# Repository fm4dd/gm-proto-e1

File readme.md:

## GM-PROTO-E1

### Description

The gm-proto-e1 board is an application module board for the <a href="https://www.colognechip.com/programmable-logic/gatemate-evaluation-board/">GateMate FPGA evaluation board E1</a>, made by <a href="https://www.colognechip.com/">Cologne Chip</a>. It connects to the evaluation board through the GPIO bank headers, and its main feature is the 20x19 standard 2.54mm pitch prototyping area. 36 FPGA signals from GPIO banks SB, EA and EB are brought in to enable easy experimentation for connecting FPGA board peripherals. In addition, the application board provides a minimal set of data input/output components for basic FPGA interactions. Two variants have been designed: One for through-hole components, one for higher density SMD parts:

- 2x push buttons THT / 3x push buttons SMD
- 4x slide switches THT / 8x DIP switches SMD
- 4x LED THT / 8x LED SMD
- 2x 7-Segment display modules
- Buzzer (SMD only)

This design is registered under the OSHWA Open Source Hardware Self-Certification:  

### Hardware Versions

The gm-proto-e1 application board has been designed as a 100x70mm double-layer PCB, with precision alignment of the six 46-pin 1.27mm pitch GPIO connectors, verified to fit the GateMate FPGA evaluation board E1 V3.1B. For THT components, great care needs to be taken to cut pins flush during soldering and prevent them from reaching components of the evaluation board below. The 1.27mm pitch GPIO connectors are offered with different distance spacers (2, 2.5 and 5mm), and the standard spacers achieve only 5mm total clearance.

#### Through-hole Design:

| Version | Gerber | Schema |
|---------|--------|--------|
| 1.0     |[20220914-gm-proto-e1-gerber.zip](fabfiles-tht/v10/20220914-gm-proto-e1-gerber.zip) | [20220914-gm-proto-e1-schematic.pdf](fabfiles-tht/v10/20220914-gm-proto-e1-schematic.pdf) |

#### Surface-Mount Design:

| Version | Gerber | Schema |
|---------|--------|--------|
| 1.0     |[20220923-gm-proto-e1-gerber.zip](fabfiles-smd/v10/20220923-gm-proto-e1-gerber.zip) | [20220923-gm-proto-e1-schematic.pdf](fabfiles-smd/v10/20220923-gm-proto-e1-schematic.pdf) |

### Pin Assignments

Due to IO differences between THT and SMD board variants, they have different pinouts:

#### Through-hole Design:

- IO pinout assigments file: [pin-assignment-tht.md](pin-assignment-tht.md)
- hardware constraints file: [gm-proto-e1-tht.ccf](examples-tht/gm-proto-e1-tht.ccf)

#### Surface-Mount Design:

- IO pinout assigments file: [pin-assignment-smd.md](pin-assignment-smd.md)
- hardware constraints file: [gm-proto-e1-smd.ccf](examples-smd/gm-proto-e10-smd.ccf)

Note: Components are prefixed with "pr", to identify them belonging to the gm-proto-e1 application board. For prototyping, 36 IO signals from GPIO banks SB, EA and EB have been placed into the 2.54mm area border pin rows.

### Example Code

The following code examples demonstrate the board input/output components for quick verification. The code has been tested with the pre-compiled opensource toolchain released through the GateMate support site at <a href="https://www.colognechip.com/mygatemate/">https://www.colognechip.com/mygatemate/</a>

#### Through-hole Design:

| Language | Folder                       | Description                                                       |
|----------|------------------------------|-------------------------------------------------------------------|
| Verilog  |[blink](examples-tht/blink)   | blinks two LED's in a alternating pattern                         |
| Verilog  |[count](examples-tht/count)   | binary counter displayed on four LED and two 7-Segment digits     |
| Verilog  |[button](examples-tht/button) | push button press changes LED frequency and light move direction  |
| Verilog  |[switch](examples-tht/switch) | each slide switch turns its corresponding LED on or off           |
| Verilog  |[display](examples-tht/display)| basic control of a HD44780-compatible 3.3V character LCD display  |
| Verilog  |[rotenc16](examples-tht/rotenc16)| basic control of a 16-position rotary encoder input switch  |

#### Surface-Mount Design:

| Language | Folder                        | Description                                                       |
|----------|-------------------------------|-------------------------------------------------------------------|
| Verilog  |[blink](examples-smd/blink)    | blinks four LED's in a alternating pattern                        |
| Verilog  |[count](examples-smd/count)    | binary counter displayed on eight LED and two 7-Segment digits    |
| Verilog  |[button](examples-smd/button)  | push button press changes LED frequency and light move direction  |
| Verilog  |[switch](examples-smd/switch)  | each slide switch turns its corresponding LED on or off           |

### Board Pictures

The gm-proto-e1 THT board, before and after assembly.

The gm-proto-e1 THT board has been designed with KiCad version 6.0.

The gm-proto-e1 THT board mounted on the E1 board, running the "count" demo.

The gm-proto-e1 THT board hardware verification video.

The gm-proto-e1 THT board, running the "display" demo

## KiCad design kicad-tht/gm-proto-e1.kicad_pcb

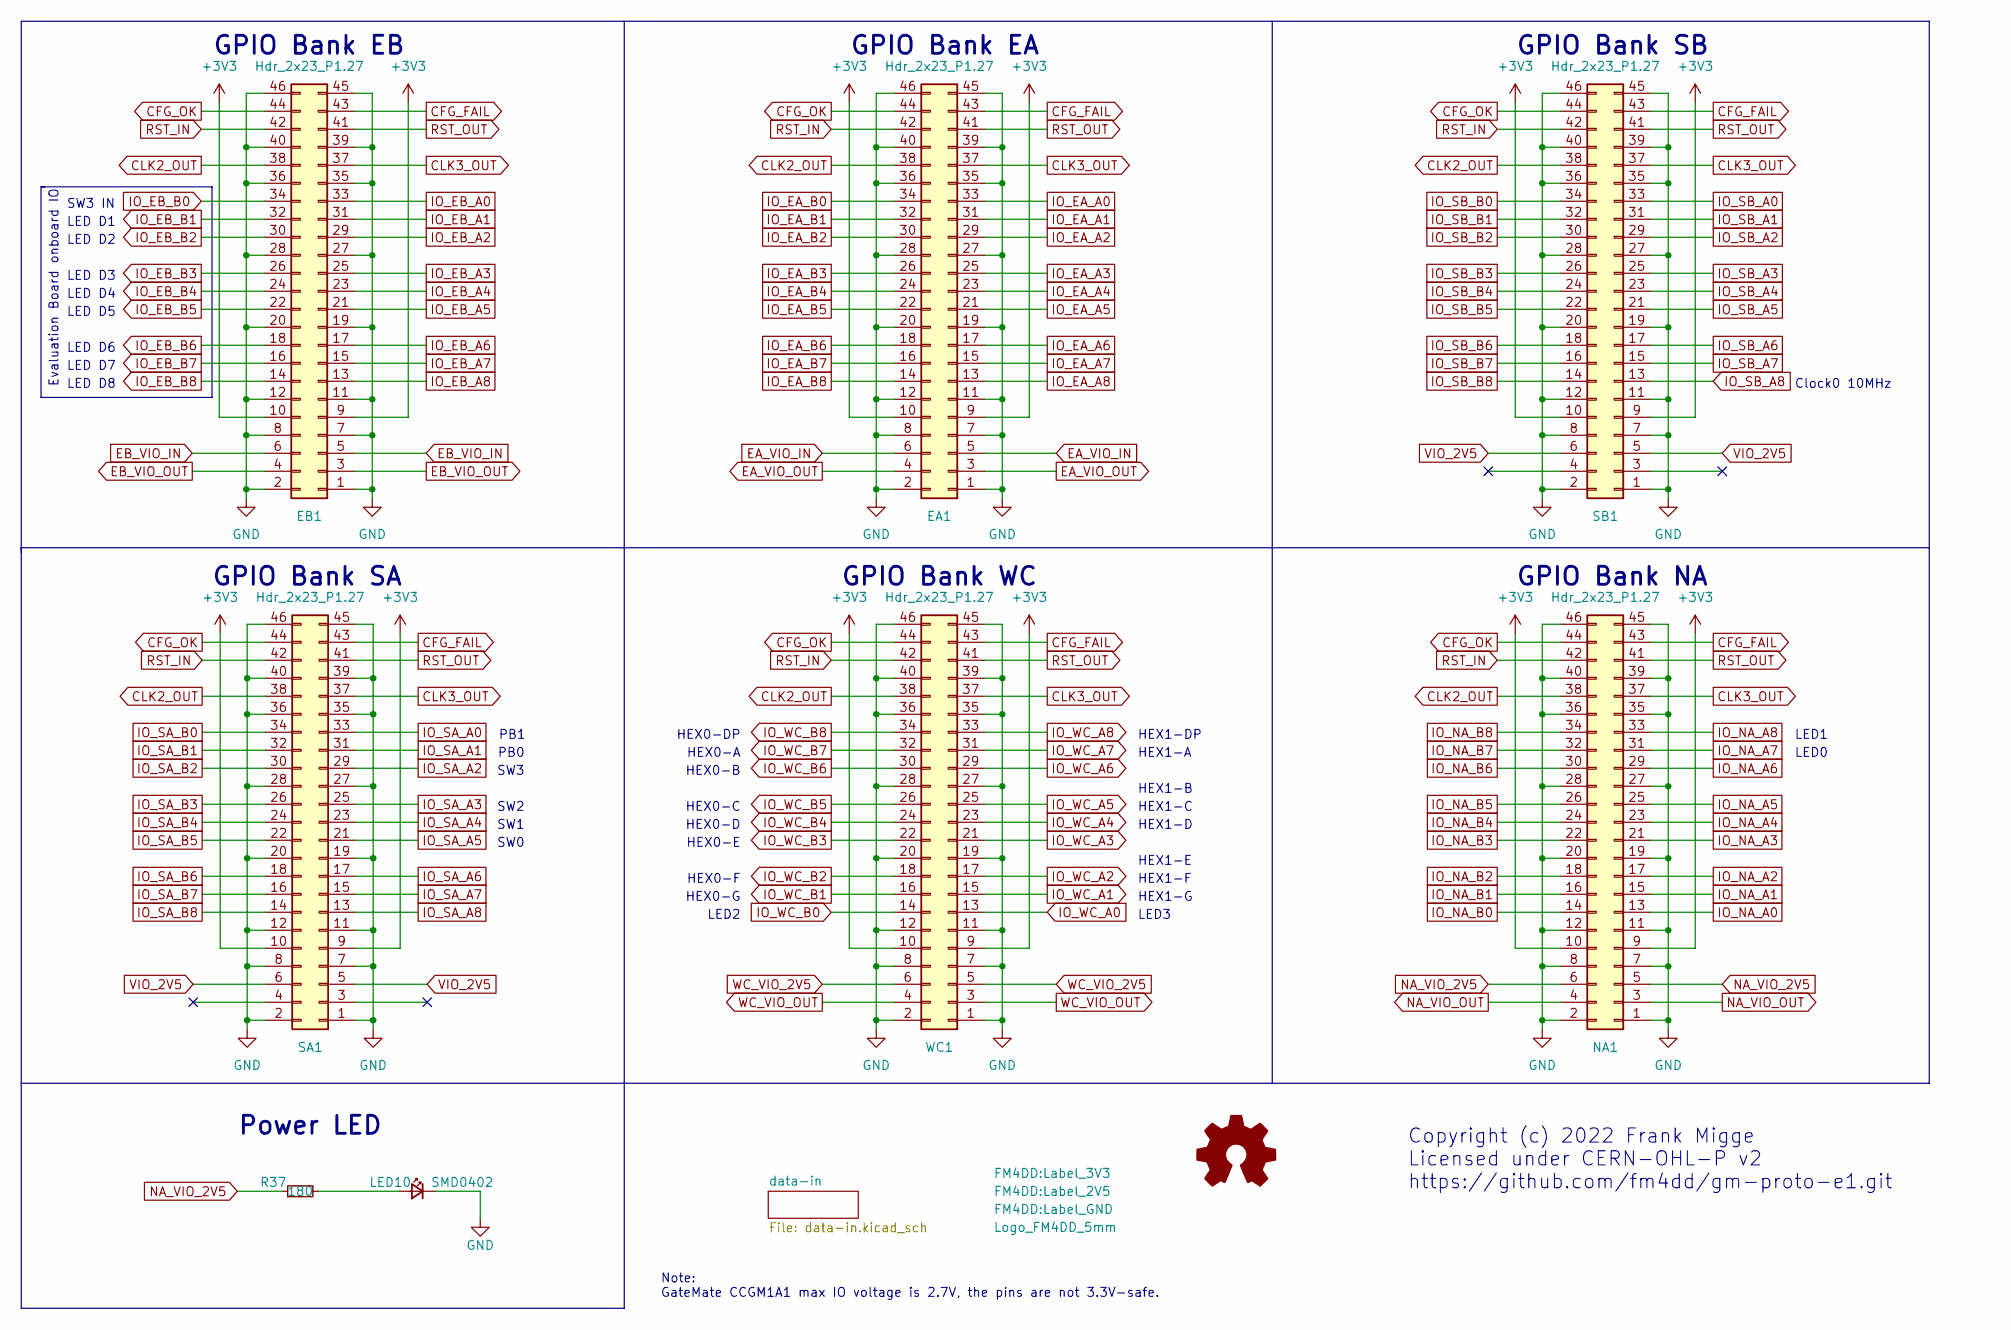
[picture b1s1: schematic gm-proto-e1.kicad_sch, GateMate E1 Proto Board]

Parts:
EA1: Hdr_2x23_P1.27; PinHeader_2x23_P1.27_backside
EB1: Hdr_2x23_P1.27; PinHeader_2x23_P1.27_backside
LB2: Label_2V5
LB3: Label_GND
LB4: Logo_FM4DD_5mm; Logo_FM4DD_5mm_SScr
LB5: Label_3V3
LED10: SMD0402; LED_D3.0mm
NA1: Hdr_2x23_P1.27; PinHeader_2x23_P1.27_backside
R37: 180; R_Axial_DIN0204_L3.6mm_D1.6mm_P5.08mm_Horizontal
SA1: Hdr_2x23_P1.27; PinHeader_2x23_P1.27_backside
SB1: Hdr_2x23_P1.27; PinHeader_2x23_P1.27_backside
WC1: Hdr_2x23_P1.27; PinHeader_2x23_P1.27_backside

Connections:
+3V3: EA1.9, EA1.10, EB1.9, EB1.10, NA1.9, NA1.10, SA1.9, SA1.10, SB1.9, SB1.10, WC1.9, WC1.10; also elsewhere on the board
CFG_FAIL: EA1.43, EB1.43, NA1.43, SA1.43, SB1.43, WC1.43
CFG_OK: EA1.44, EB1.44, NA1.44, SA1.44, SB1.44, WC1.44
CLK2_OUT: EA1.38, EB1.38, NA1.38, SA1.38, SB1.38, WC1.38
CLK3_OUT: EA1.37, EB1.37, NA1.37, SA1.37, SB1.37, WC1.37
EA_VIO_IN: EA1.5, EA1.6
EA_VIO_OUT: EA1.3, EA1.4
EB_VIO_IN: EB1.5, EB1.6; also elsewhere on the board
EB_VIO_OUT: EB1.3, EB1.4
IO_EA_A0: EA1.33; also elsewhere on the board
IO_EA_A1: EA1.31; also elsewhere on the board
IO_EA_A2: EA1.29; also elsewhere on the board
IO_EA_A3: EA1.25; also elsewhere on the board
IO_EA_A4: EA1.23; also elsewhere on the board
IO_EA_A5: EA1.21; also elsewhere on the board
IO_EA_A6: EA1.17; also elsewhere on the board
IO_EA_A7: EA1.15; also elsewhere on the board
IO_EA_A8: EA1.13; also elsewhere on the board
IO_EA_B0: EA1.34
IO_EA_B1: EA1.32
IO_EA_B2: EA1.30
IO_EA_B3: EA1.26
IO_EA_B4: EA1.24
IO_EA_B5: EA1.22
IO_EA_B6: EA1.18
IO_EA_B7: EA1.16
IO_EA_B8: EA1.14
IO_EB_A0: EB1.33; also elsewhere on the board
IO_EB_A1: EB1.31; also elsewhere on the board
IO_EB_A2: EB1.29; also elsewhere on the board
IO_EB_A3: EB1.25; also elsewhere on the board
IO_EB_A4: EB1.23; also elsewhere on the board
IO_EB_A5: EB1.21; also elsewhere on the board
IO_EB_A6: EB1.17; also elsewhere on the board
IO_EB_A7: EB1.15; also elsewhere on the board
IO_EB_A8: EB1.13; also elsewhere on the board
IO_EB_B0: EB1.34
IO_EB_B1: EB1.32
IO_EB_B2: EB1.30
IO_EB_B3: EB1.26
IO_EB_B4: EB1.24
IO_EB_B5: EB1.22
IO_EB_B6: EB1.18
IO_EB_B7: EB1.16
IO_EB_B8: EB1.14
IO_NA_A0: NA1.13
IO_NA_A1: NA1.15
IO_NA_A2: NA1.17
IO_NA_A3: NA1.21
IO_NA_A4: NA1.23
IO_NA_A5: NA1.25
IO_NA_A6: NA1.29
IO_NA_A7: NA1.31; also elsewhere on the board
IO_NA_A8: NA1.33; also elsewhere on the board
IO_NA_B0: NA1.14
IO_NA_B1: NA1.16
IO_NA_B2: NA1.18
IO_NA_B3: NA1.22
IO_NA_B4: NA1.24
IO_NA_B5: NA1.26
IO_NA_B6: NA1.30
IO_NA_B7: NA1.32
IO_NA_B8: NA1.34
IO_SA_A0: SA1.33; also elsewhere on the board
IO_SA_A1: SA1.31; also elsewhere on the board
IO_SA_A2: SA1.29; also elsewhere on the board
IO_SA_A3: SA1.25; also elsewhere on the board
IO_SA_A4: SA1.23; also elsewhere on the board
IO_SA_A5: SA1.21; also elsewhere on the board
IO_SA_A6: SA1.17
IO_SA_A7: SA1.15
IO_SA_A8: SA1.13
IO_SA_B0: SA1.34
IO_SA_B1: SA1.32
IO_SA_B2: SA1.30
IO_SA_B3: SA1.26
IO_SA_B4: SA1.24
IO_SA_B5: SA1.22
IO_SA_B6: SA1.18
IO_SA_B7: SA1.16
IO_SA_B8: SA1.14
IO_SB_A0: SB1.33; also elsewhere on the board
IO_SB_A1: SB1.31; also elsewhere on the board
IO_SB_A2: SB1.29; also elsewhere on the board
IO_SB_A3: SB1.25; also elsewhere on the board
IO_SB_A4: SB1.23; also elsewhere on the board
IO_SB_A5: SB1.21; also elsewhere on the board
IO_SB_A6: SB1.17; also elsewhere on the board
IO_SB_A7: SB1.15; also elsewhere on the board
IO_SB_A8: SB1.13; also elsewhere on the board
IO_SB_B0: SB1.34; also elsewhere on the board
IO_SB_B1: SB1.32; also elsewhere on the board
IO_SB_B2: SB1.30; also elsewhere on the board
IO_SB_B3: SB1.26; also elsewhere on the board
IO_SB_B4: SB1.24; also elsewhere on the board
IO_SB_B5: SB1.22; also elsewhere on the board
IO_SB_B6: SB1.18; also elsewhere on the board
IO_SB_B7: SB1.16; also elsewhere on the board
IO_SB_B8: SB1.14; also elsewhere on the board
IO_WC_A0: WC1.13; also elsewhere on the board
IO_WC_A1: WC1.15; also elsewhere on the board
IO_WC_A2: WC1.17; also elsewhere on the board
IO_WC_A3: WC1.21; also elsewhere on the board
IO_WC_A4: WC1.23; also elsewhere on the board
IO_WC_A5: WC1.25; also elsewhere on the board
IO_WC_A6: WC1.29; also elsewhere on the board
IO_WC_A7: WC1.31; also elsewhere on the board
IO_WC_A8: WC1.33; also elsewhere on the board
IO_WC_B0: WC1.14; also elsewhere on the board
IO_WC_B1: WC1.16; also elsewhere on the board
IO_WC_B2: WC1.18; also elsewhere on the board
IO_WC_B3: WC1.22; also elsewhere on the board
IO_WC_B4: WC1.24; also elsewhere on the board
IO_WC_B5: WC1.26; also elsewhere on the board
IO_WC_B6: WC1.30; also elsewhere on the board
IO_WC_B7: WC1.32; also elsewhere on the board
IO_WC_B8: WC1.34; also elsewhere on the board
NA_VIO_2V5: NA1.5, NA1.6, R37.1; also elsewhere on the board
NA_VIO_OUT: NA1.3, NA1.4
unnamed: LED10.2 (A), R37.2
RST_IN: EA1.42, EB1.42, NA1.42, SA1.42, SB1.42, WC1.42
RST_OUT: EA1.41, EB1.41, NA1.41, SA1.41, SB1.41, WC1.41
VIO_2V5: SA1.5, SA1.6, SB1.5, SB1.6; also elsewhere on the board
WC_VIO_OUT: WC1.3, WC1.4

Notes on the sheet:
HEX0-A
SW1
LED1
HEX0-B
HEX0-E
LED D3
Note: GateMate CCGM1A1 max IO voltage is 2.7V, the pins are not 3.3V-safe.
LED D7
LED D2
HEX1-F
SW3 IN
HEX0-F
LED D8
Clock0 10MHz
LED D4
HEX1-G
SW0
GPIO Bank NA
LED2
Evaluation Board onboard IO
SW3
HEX1-D
HEX0-C
GPIO Bank SB
GPIO Bank SA
PB0
PB1
HEX0-G
HEX1-A
GPIO Bank EB
HEX0-DP
LED D5
HEX1-C
LED D6
HEX1-E
GPIO Bank WC
HEX1-DP
LED D1
Copyright (c) 2022 Frank Migge Licensed under CERN-OHL-P v2 https://github.com/fm4dd/gm-proto-e1.git
HEX1-B

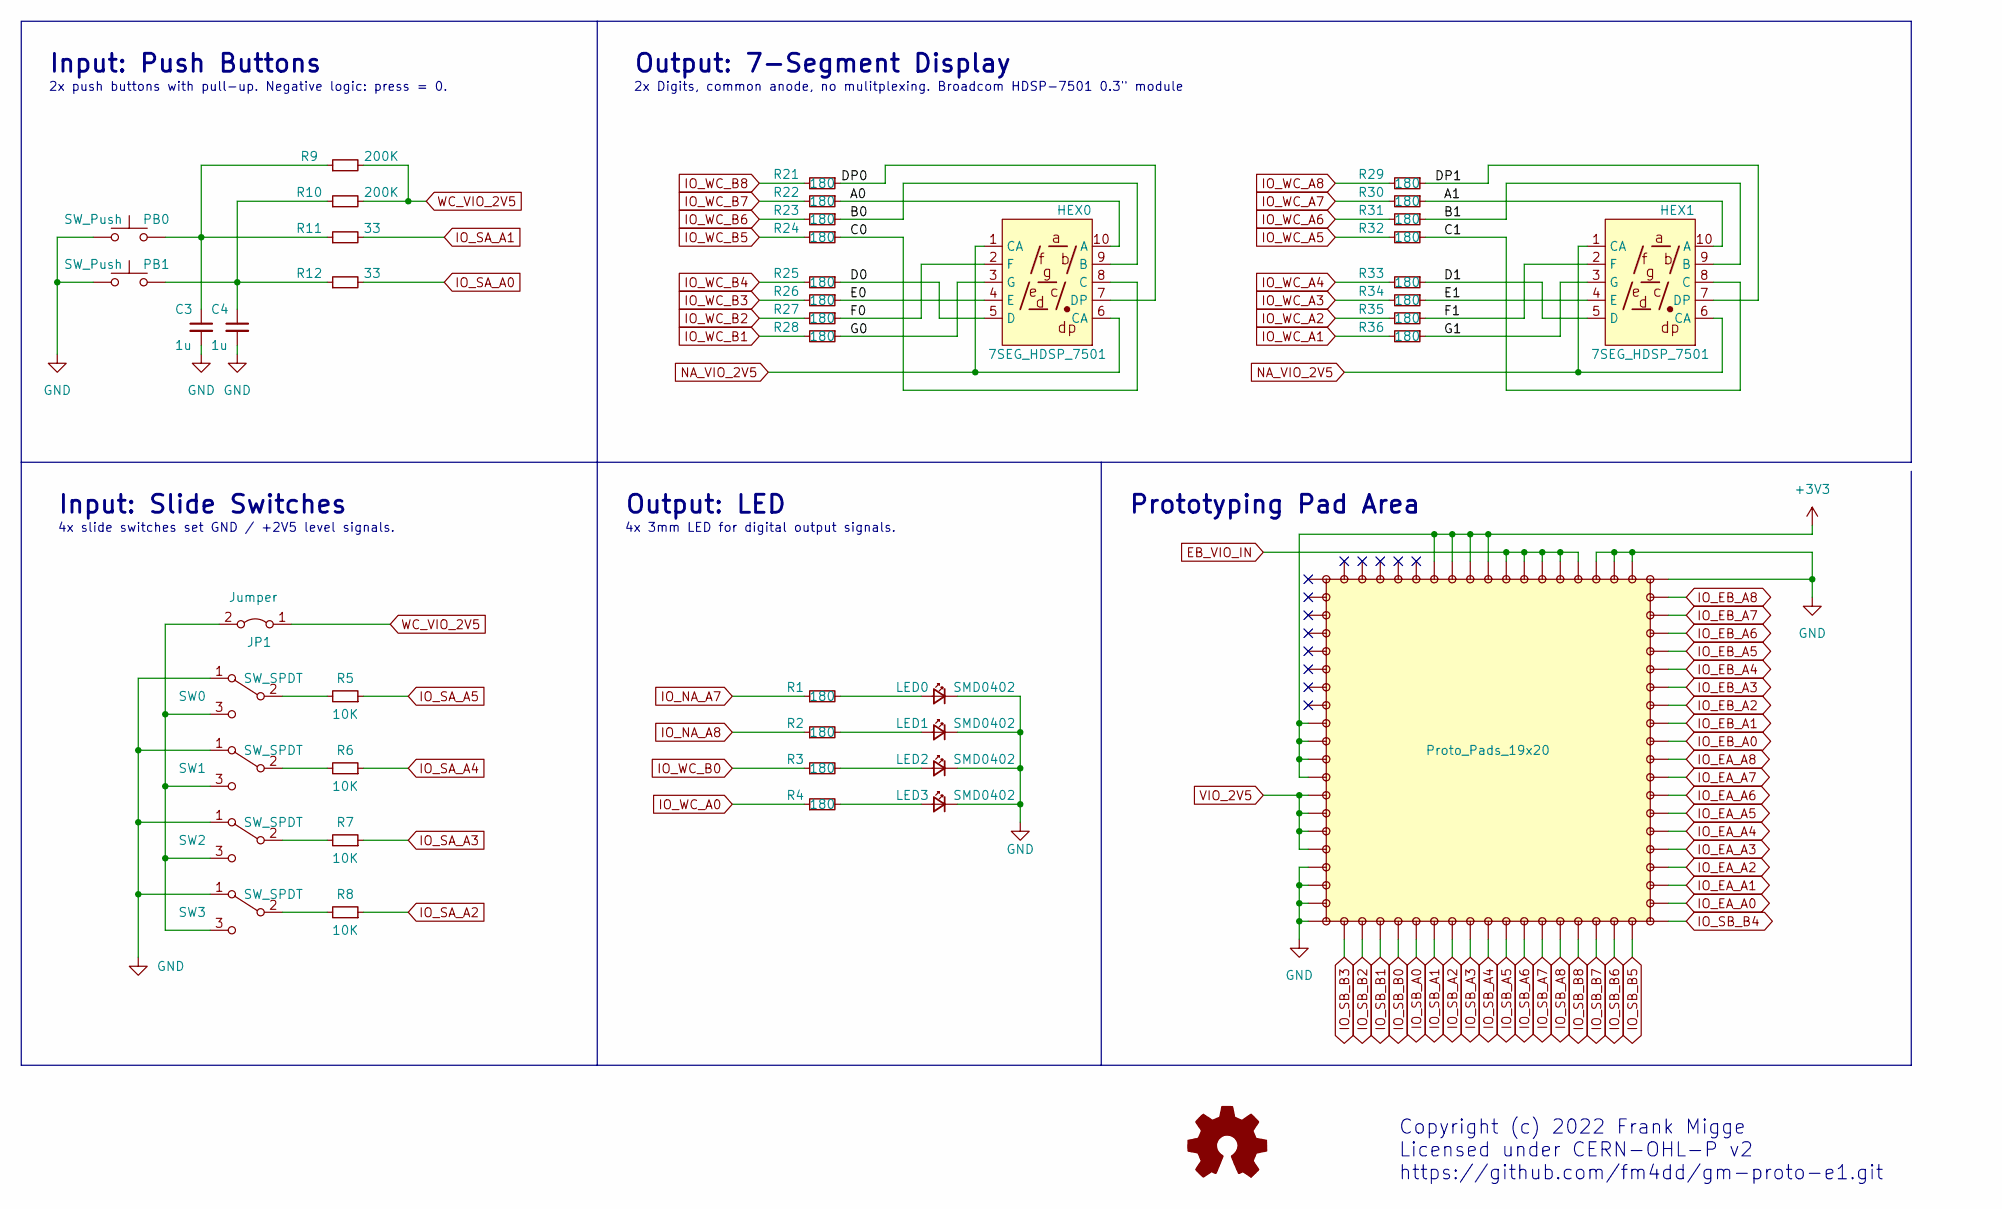
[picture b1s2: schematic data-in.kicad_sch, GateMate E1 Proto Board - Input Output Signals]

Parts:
C3, C4: 1u; C_Disc_D5.0mm_W2.5mm_P2.50mm
H1: Proto_Pads_19x20; Proto_Pad_Array_19x20
HEX0, HEX1: 7SEG_HDSP_7501; HDSP-7401
JP1: Jumper; PinHeader_1x02_P2.54mm_Vertical
LED0, LED1, LED2, LED3: SMD0402; LED_D3.0mm
PB0, PB1: SW_Push; SW_PUSH_6mm
R1, R2, R3, R4, R21, R22, R23, R24, R25, R26, R27, R28, R29, R30, R31, R32, R33, R34, R35, R36: 180; R_Axial_DIN0204_L3.6mm_D1.6mm_P5.08mm_Horizontal
R5, R6, R7, R8: 10K; R_Axial_DIN0204_L3.6mm_D1.6mm_P5.08mm_Horizontal
R9, R10: 200K; R_Axial_DIN0204_L3.6mm_D1.6mm_P5.08mm_Horizontal
R11, R12: 33; R_Axial_DIN0204_L3.6mm_D1.6mm_P5.08mm_Horizontal
SW0, SW1, SW2, SW3: SW_SPDT; SlideSW_SS12-D01

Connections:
+3V3: H1.29 (p29), H1.30 (p30), H1.31 (p31), H1.32 (p32), H1.46 (p46), H1.47 (p47), H1.48 (p48), H1.49 (p49); also elsewhere on the board
/data-in/A0: HEX0.10 (A), R22.1
/data-in/A1: HEX1.10 (A), R30.1
/data-in/B0: HEX0.9 (B), R23.1
/data-in/B1: HEX1.9 (B), R31.1
/data-in/C0: HEX0.8 (C), R24.1
/data-in/C1: HEX1.8 (C), R32.1
/data-in/D0: HEX0.5 (D), R25.1
/data-in/D1: HEX1.5 (D), R33.1
/data-in/DP0: HEX0.7 (DP), R21.1
/data-in/DP1: HEX1.7 (DP), R29.1
/data-in/E0: HEX0.4 (E), R26.1
/data-in/E1: HEX1.4 (E), R34.1
/data-in/F0: HEX0.2 (F), R27.1
/data-in/F1: HEX1.2 (F), R35.1
/data-in/G0: HEX0.3 (G), R28.1
/data-in/G1: HEX1.3 (G), R36.1
EB_VIO_IN: H1.24 (p24), H1.25 (p25), H1.26 (p26), H1.27 (p27), H1.28 (p28); also elsewhere on the board
IO_EA_A0: H1.2 (p2); also elsewhere on the board
IO_EA_A1: H1.3 (p3); also elsewhere on the board
IO_EA_A2: H1.4 (p4); also elsewhere on the board
IO_EA_A3: H1.5 (p5); also elsewhere on the board
IO_EA_A4: H1.6 (p6); also elsewhere on the board
IO_EA_A5: H1.7 (p7); also elsewhere on the board
IO_EA_A6: H1.8 (p8); also elsewhere on the board
IO_EA_A7: H1.9 (p9); also elsewhere on the board
IO_EA_A8: H1.10 (p10); also elsewhere on the board
IO_EB_A0: H1.11 (p11); also elsewhere on the board
IO_EB_A1: H1.12 (p12); also elsewhere on the board
IO_EB_A2: H1.13 (p13); also elsewhere on the board
IO_EB_A3: H1.14 (p14); also elsewhere on the board
IO_EB_A4: H1.15 (p15); also elsewhere on the board
IO_EB_A5: H1.16 (p16); also elsewhere on the board
IO_EB_A6: H1.17 (p17); also elsewhere on the board
IO_EB_A7: H1.18 (p18); also elsewhere on the board
IO_EB_A8: H1.19 (p19); also elsewhere on the board
IO_NA_A7: R1.1; also elsewhere on the board
IO_NA_A8: R2.1; also elsewhere on the board
IO_SA_A0: R12.2; also elsewhere on the board
IO_SA_A1: R11.2; also elsewhere on the board
IO_SA_A2: R8.1; also elsewhere on the board
IO_SA_A3: R7.1; also elsewhere on the board
IO_SA_A4: R6.1; also elsewhere on the board
IO_SA_A5: R5.1; also elsewhere on the board
IO_SB_A0: H1.62 (p62); also elsewhere on the board
IO_SB_A1: H1.63 (p63); also elsewhere on the board
IO_SB_A2: H1.64 (p64); also elsewhere on the board
IO_SB_A3: H1.65 (p65); also elsewhere on the board
IO_SB_A4: H1.66 (p66); also elsewhere on the board
IO_SB_A5: H1.67 (p67); also elsewhere on the board
IO_SB_A6: H1.68 (p68); also elsewhere on the board
IO_SB_A7: H1.69 (p69); also elsewhere on the board
IO_SB_A8: H1.70 (p70); also elsewhere on the board
IO_SB_B0: H1.61 (p61); also elsewhere on the board
IO_SB_B1: H1.60 (p60); also elsewhere on the board
IO_SB_B2: H1.59 (p59); also elsewhere on the board
IO_SB_B3: H1.58 (p58); also elsewhere on the board
IO_SB_B4: H1.1 (p1); also elsewhere on the board
IO_SB_B5: H1.74 (p74); also elsewhere on the board
IO_SB_B6: H1.73 (p73); also elsewhere on the board
IO_SB_B7: H1.72 (p72); also elsewhere on the board
IO_SB_B8: H1.71 (p71); also elsewhere on the board
IO_WC_A0: R4.1; also elsewhere on the board
IO_WC_A1: R36.2; also elsewhere on the board
IO_WC_A2: R35.2; also elsewhere on the board
IO_WC_A3: R34.2; also elsewhere on the board
IO_WC_A4: R33.2; also elsewhere on the board
IO_WC_A5: R32.2; also elsewhere on the board
IO_WC_A6: R31.2; also elsewhere on the board
IO_WC_A7: R30.2; also elsewhere on the board
IO_WC_A8: R29.2; also elsewhere on the board
IO_WC_B0: R3.1; also elsewhere on the board
IO_WC_B1: R28.2; also elsewhere on the board
IO_WC_B2: R27.2; also elsewhere on the board
IO_WC_B3: R26.2; also elsewhere on the board
IO_WC_B4: R25.2; also elsewhere on the board
IO_WC_B5: R24.2; also elsewhere on the board
IO_WC_B6: R23.2; also elsewhere on the board
IO_WC_B7: R22.2; also elsewhere on the board
IO_WC_B8: R21.2; also elsewhere on the board
NA_VIO_2V5: HEX0.1 (CA), HEX0.6 (CA), HEX1.1 (CA), HEX1.6 (CA); also elsewhere on the board
unnamed: C3.1, PB0.2, R9.1, R11.1
unnamed: C4.1, PB1.2, R10.1, R12.1
unnamed: LED0.2 (A), R1.2
unnamed: LED1.2 (A), R2.2
unnamed: LED2.2 (A), R3.2
unnamed: LED3.2 (A), R4.2
unnamed: R5.2, SW0.2 (B)
unnamed: R6.2, SW1.2 (B)
unnamed: R7.2, SW2.2 (B)
unnamed: R8.2, SW3.2 (B)
VIO_2V5: H1.50 (p50), H1.51 (p51), H1.52 (p52), H1.53 (p53); also elsewhere on the board

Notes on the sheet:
Prototyping Pad Area
Copyright (c) 2022 Frank Migge Licensed under CERN-OHL-P v2 https://github.com/fm4dd/gm-proto-e1.git
2x push buttons with pull-up. Negative logic: press = 0.
Input: Push Buttons
4x slide switches set GND / +2V5 level signals.
Input: Slide Switches
4x 3mm LED for digital output signals.
Output: 7-Segment Display
Output: LED
2x Digits, common anode, no mulitplexing. Broadcom HDSP-7501 0.3" module

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
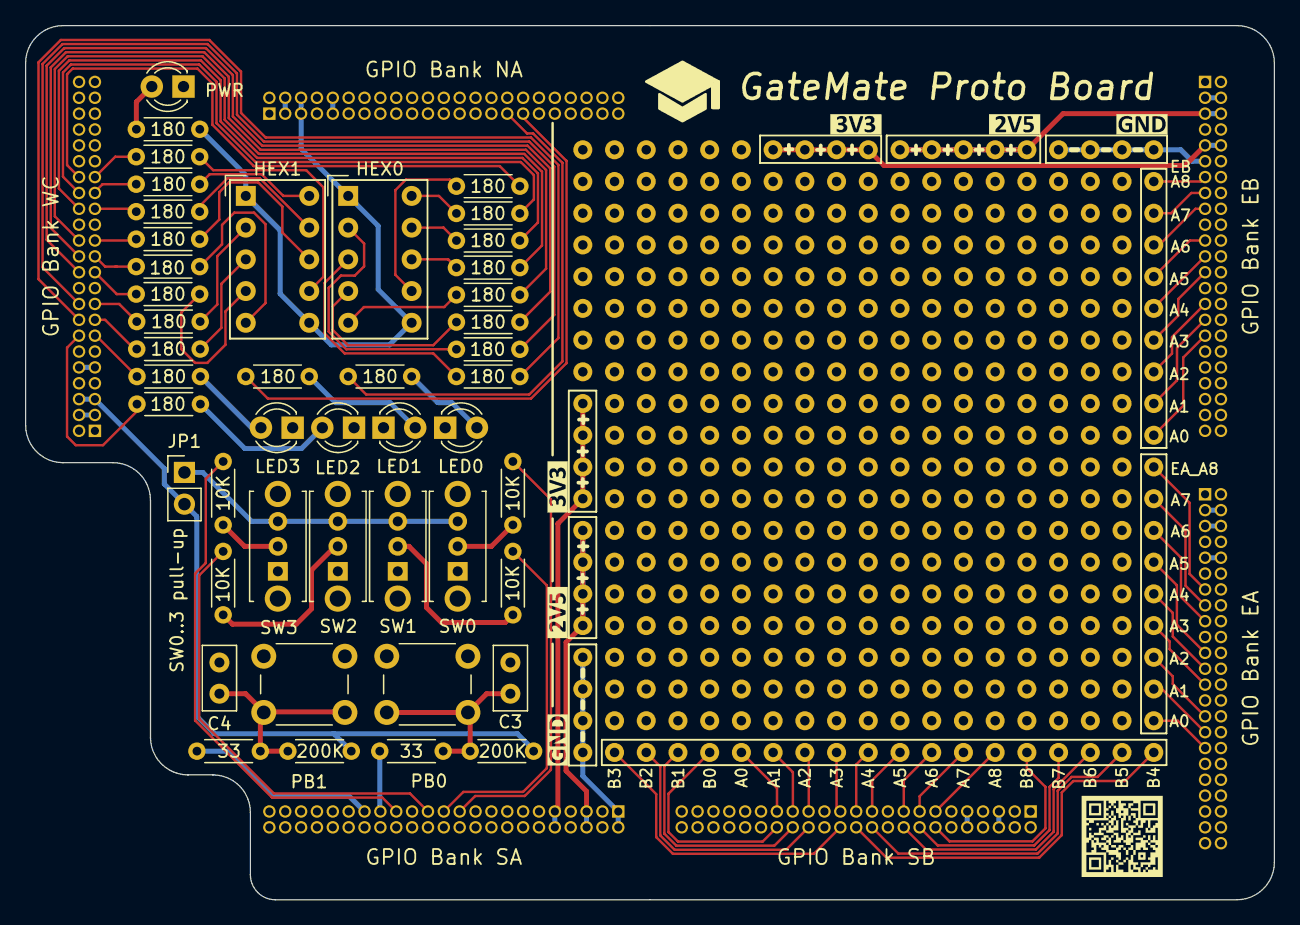
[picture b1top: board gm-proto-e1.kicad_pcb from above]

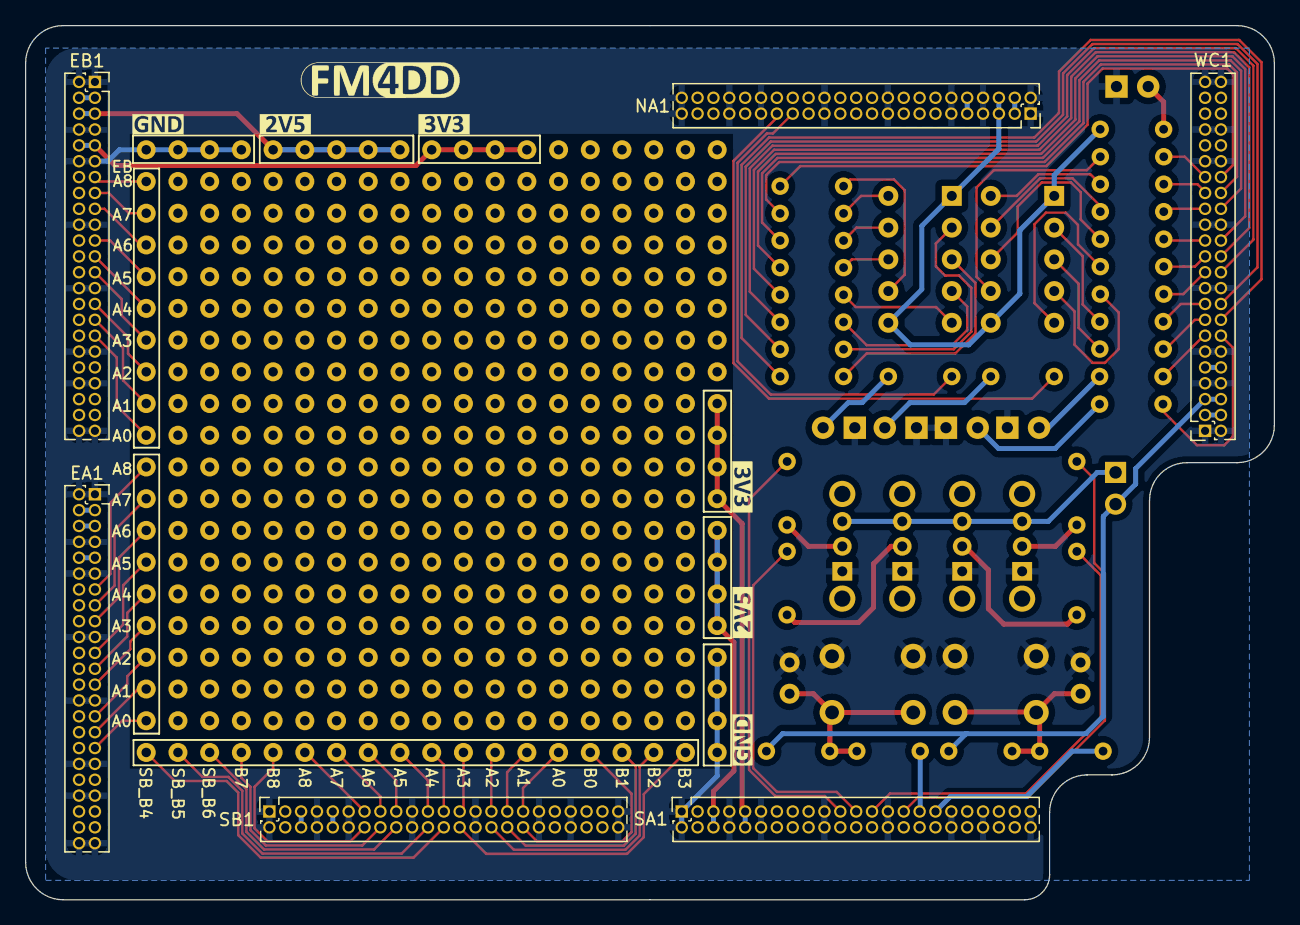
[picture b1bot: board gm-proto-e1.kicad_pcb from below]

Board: 2 copper layers, 100.0 x 70.0 mm, 65 parts (13 on the bottom side), 107 nets.

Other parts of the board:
LB6, LB7, LB8: Label_3V3
LB21, LB25, LB25#2: Label_2V5
LB31, LB33, LB33#2: Label_GND

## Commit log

2022-09-18 repo init
2022-09-23 add SMD version
2022-09-24 smd schema text fixes
2022-09-26 1st demo code
2022-09-27 assembly and tests
2022-10-09 add verilog examples
2022-10-10 add display demo
2022-10-10 add smd examples
2022-10-16 fix blink src, add display schema
2022-11-06 add buzzer sound examples
2023-05-29 add rotary encoder
2024-02-18 add 8-bit LCD example
